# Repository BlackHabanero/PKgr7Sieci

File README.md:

# Projekt kompetencyjny grupa 7 - "Sieci przemysłowe"
Stworzyliśmy sieć przemysłową złożoną z CAN, EIA485, światłowodu oraz podsieci radiowej
w salach na trzecim piętrze budynku CTI Politechniki Łódzkiej

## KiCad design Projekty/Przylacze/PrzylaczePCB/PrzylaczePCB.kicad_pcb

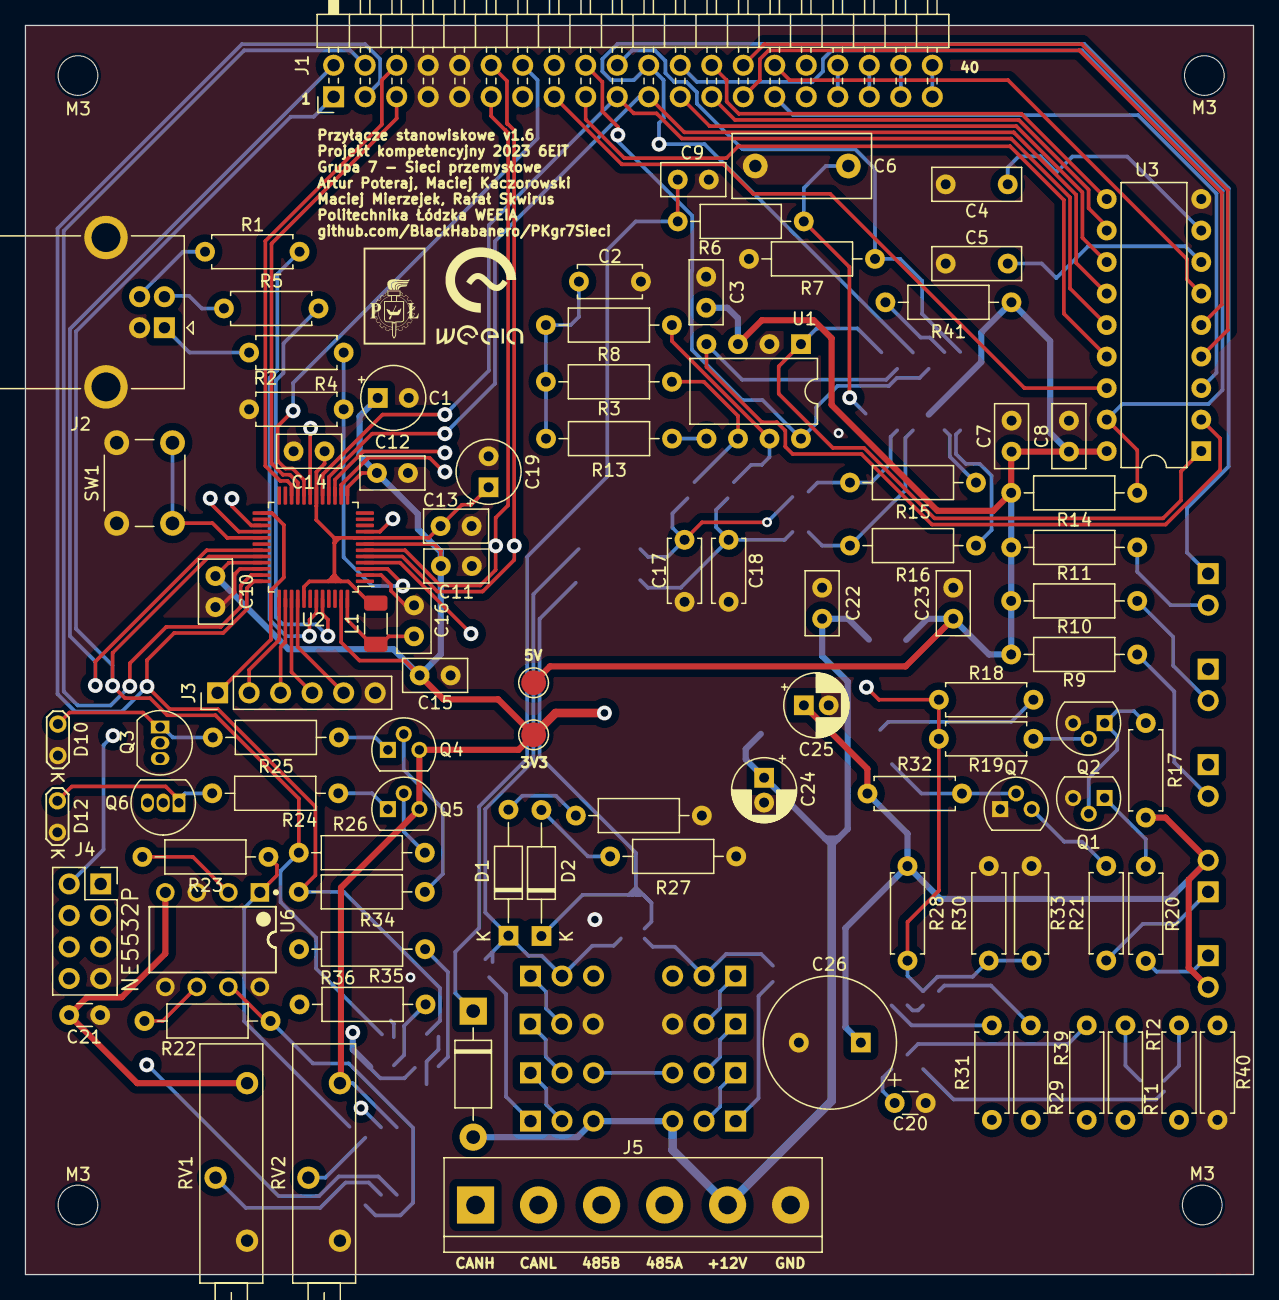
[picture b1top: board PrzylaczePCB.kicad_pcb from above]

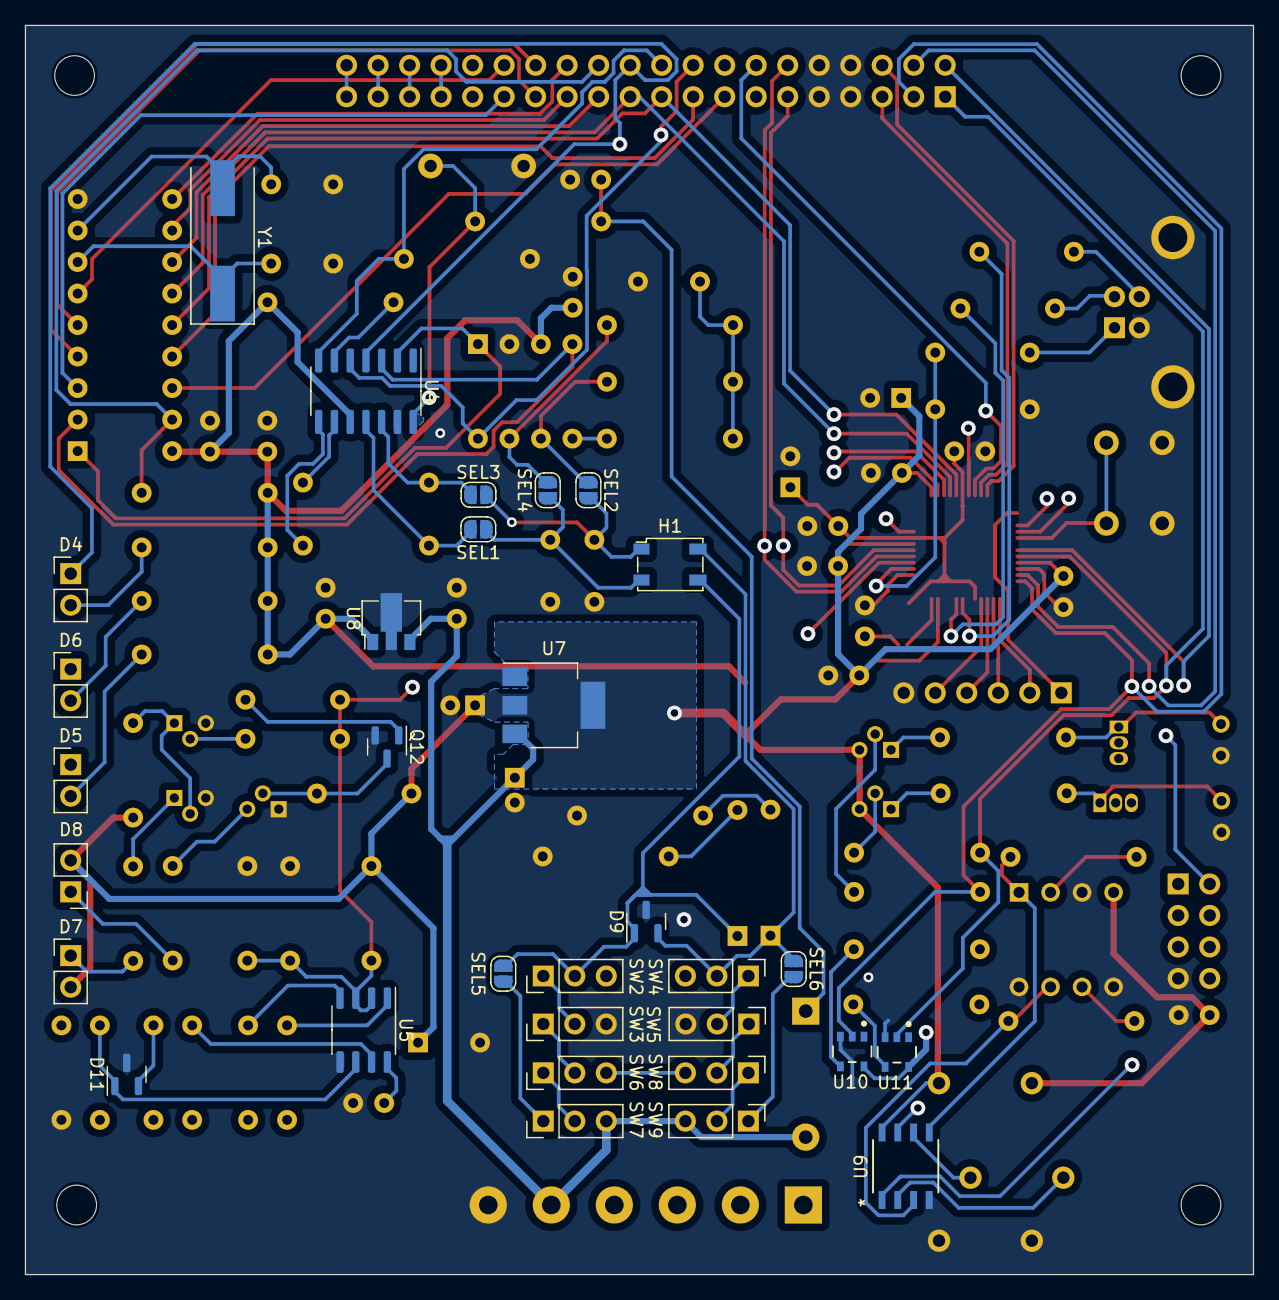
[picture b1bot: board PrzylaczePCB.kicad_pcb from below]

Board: 4 copper layers, 99.0 x 100.7 mm, 127 parts (31 on the bottom side), 104 nets.

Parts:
C1: 4.7μ; CP_Radial_Tantal_D5.0mm_P2.50mm
C2: 4n7; C_Disc_D5.0mm_W2.5mm_P5.00mm
C3, C7, C8, C9, C10, C11, C12, C13, C14, C15, C16, C23: 100n; C_Disc_D5.0mm_W2.5mm_P2.50mm
C4, C5: 15p; C_Disc_D7.0mm_W2.5mm_P5.00mm
C6: 10n; C_Disc_D11.0mm_W5.0mm_P7.50mm
C17, C18: 150p; C_Disc_D5.0mm_W2.5mm_P5.00mm
C19: 2.2μ; CP_Radial_Tantal_D5.0mm_P2.50mm
C20: 0.1 uF; C_Disc_D3.0mm_W1.6mm_P2.50mm
C21: 100n; C_Disc_D3.0mm_W1.6mm_P2.50mm
C22: 330n; C_Disc_D5.0mm_W2.5mm_P2.50mm
C24: 1u; CP_Radial_D5.0mm_P2.00mm
C25: 4.7u; CP_Radial_D5.0mm_P2.00mm
C26: 10 uF; CP_Radial_Tantal_D10.5mm_P5.00mm
D1, D2: Zener 10V; D_DO-35_SOD27_P10.16mm_Horizontal
D3: 1N4001; D_DO-41_SOD81_P10.16mm_Horizontal
D4, D5, D6: LED; PinHeader_1x02_P2.54mm_Vertical
D7: LTL-307ELC; PinHeader_1x02_P2.54mm_Vertical
D8: L-7113LYD; PinHeader_1x02_P2.54mm_Vertical
D9: PESD2IVN24-TR; SOT-23
D10, D12: LED; TestPoint_2Pads_Pitch2.54mm_Drill0.8mm
D11: SM712_SOT23; SOT-23
H1: B82787C0104H002; 4Pin_COMMON_MODE_CHOKE_B82787C0104H002
J1: Conn_02x20_Odd_Even; PinHeader_2x20_P2.54mm_Horizontal
J2: USB_B; USB_B_OST_USB-B1HSxx_Horizontal
J3: Conn_01x06; PinHeader_1x06_P2.54mm_Vertical
J4: Conn_02x04_Odd_Even; PinSocket_2x04_P2.54mm_Vertical
J5: Screw_Terminal_01x06; TerminalBlock_bornier-6_P5.08mm
L1: 10u; L_1206_3216Metric_Pad1.22x1.90mm_HandSolder
M3, M3#2, M3#3, M3#4: MountingHole_3.2mm_M3
Q1, Q2: BC547; TO-92L
Q3, Q6: BC547; TO-92_Inline
Q4, Q5: 2N3904; TO-92L
Q7: BC557; TO-92L
Q12: 2N7002; SOT-23
R1, R5: 27; R_Axial_DIN0207_L6.3mm_D2.5mm_P7.62mm_Horizontal
R2: 27k; R_Axial_DIN0207_L6.3mm_D2.5mm_P7.62mm_Horizontal
R3, R8: 62; R_Axial_DIN0207_L6.3mm_D2.5mm_P10.16mm_Horizontal
R4: 47k; R_Axial_DIN0207_L6.3mm_D2.5mm_P7.62mm_Horizontal
R6: 1-2k; R_Axial_DIN0207_L6.3mm_D2.5mm_P10.16mm_Horizontal
R7: 1k; R_Axial_DIN0207_L6.3mm_D2.5mm_P10.16mm_Horizontal
R9: R(D); R_Axial_DIN0207_L6.3mm_D2.5mm_P10.16mm_Horizontal
R10: R(D)/750; R_Axial_DIN0207_L6.3mm_D2.5mm_P10.16mm_Horizontal
R11: R(D3); R_Axial_DIN0207_L6.3mm_D2.5mm_P10.16mm_Horizontal
R12, R27: 1; R_Axial_DIN0207_L6.3mm_D2.5mm_P10.16mm_Horizontal
R13: 300; R_Axial_DIN0207_L6.3mm_D2.5mm_P10.16mm_Horizontal
R14, R26, R34, R41: 10k; R_Axial_DIN0207_L6.3mm_D2.5mm_P10.16mm_Horizontal
R15: Rrtl; R_Axial_DIN0207_L6.3mm_D2.5mm_P10.16mm_Horizontal
R16: Rrth; R_Axial_DIN0207_L6.3mm_D2.5mm_P10.16mm_Horizontal
R17, R18, R19: 1.8k; R_Axial_DIN0207_L6.3mm_D2.5mm_P7.62mm_Horizontal
R20, R21, R39, R40: 750; R_Axial_DIN0207_L6.3mm_D2.5mm_P7.62mm_Horizontal
R22, R23: 1M; R_Axial_DIN0207_L6.3mm_D2.5mm_P10.16mm_Horizontal
R24, R25: R; R_Axial_DIN0207_L6.3mm_D2.5mm_P10.16mm_Horizontal
R28: 36k; R_Axial_DIN0207_L6.3mm_D2.5mm_P7.62mm_Horizontal
R29, R30, R31, R33: 10k; R_Axial_DIN0207_L6.3mm_D2.5mm_P7.62mm_Horizontal
R32: 18k; R_Axial_DIN0207_L6.3mm_D2.5mm_P7.62mm_Horizontal
R35, R36: 600; R_Axial_DIN0207_L6.3mm_D2.5mm_P10.16mm_Horizontal
RT1, RT2: 62; R_Axial_DIN0207_L6.3mm_D2.5mm_P7.62mm_Horizontal
RV1, RV2: 20k; Potentiometer_Bourns_3006P_Horizontal
SEL1, SEL2, SEL3, SEL4, SEL5, SEL6: SolderJumper-2_P1.3mm_Open_RoundedPad1.0x1.5mm
SW1: SW_Push; SW_PUSH_6mm
SW2, SW3, SW4, SW5, SW6, SW7, SW8, SW9: SW_SPDT; PinHeader_1x03_P2.54mm_Vertical
U1: MCP2561-E-P; DIP-8_W7.62mm
U2: ATSAM4S2AA-AU; LQFP-48_7x7mm_P0.5mm
U3: MCP2515-xSO; DIP-18_W7.62mm
U4: TJA1055T_3_C,518; SO-14_3.9x8.65mm_P1.27mm
U5: MAX3485; SO-8_3.9x4.9mm_P1.27mm
U6: NE5532P; Texas_Instruments-NE5532P
U7: LDL1117S33R; SOT-223-3_TabPin2
U8: DI78M05UAB; SOT-89-3
U9: TLV3202AID
U10, U11: 74AHC1G04; Nexperia-SOT753-10_2018-0-0
Y1: 20MHz; Crystal_SMD_HC49-SD

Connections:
+3.3V: C1.1, C10.1, C11.1, C12.1, C15.1, C20.1, C21.2, C25.1, C26.1, D7.2 (A), D8.2 (A), J4.6, J4.8, Q4.3 (C), Q5.3 (C), R17.2, R28.1, R29.1, R31.1, R32.1, R39.1, RV1.1, RV2.1, U2.7 (VDDIN), U2.13 (VDDIO), U2.33 (VDDIO), U2.47 (VDDIO), U5.8 (VCC), U6.4 (VCC-), U7.2 (Vout), U9.8 (VCC), U10.5 (VCC), U11.5 (VCC)
+5V: C3.2, C7.2, C8.2, C23.1, R9.2, R10.2, R11.2, R14.2, R41.1, U1.3 (VDD), U3.18 (VDD), U4.10 (VCC), U8.1 (Vout)
+12V: C22.2, C24.1, D3.2 (A), J5.5, SW7.3 (C), SW9.3 (C), U7.3 (Vin), U8.3 (Vin)
A: D11.1 (A1), J1.35, J1.36, J5.4, R40.1, RT2.2, U5.6 (A)
B: D11.2 (A2), J1.33, J1.34, J5.3, R39.2, RT1.1, U5.7 (B)
CANH: J1.37, J1.38, J5.1, SEL6.2, SW9.1 (A)
CANH_FT: R16.2, SEL1.1, U4.11 (CANH)
CANH_HS: R8.1, SEL4.1, U1.7 (CANH)
CANL: J1.39, J1.40, J5.2, SEL5.2, SW7.1 (A)
CANL_FT: R15.2, SEL3.1, U4.12 (CANL)
CANL_HS: R3.2, SEL2.1, U1.6 (CANL)
CS0: J1.14, J4.5, U2.20 (PA11/PGMM3)
CS3: J1.15, U2.27 (PA5/PGMRDY), U3.16 (~CS)
EN: J1.16, R41.2, U2.15 (PA15/PGMD3), U4.6 (EN)
ERR: D4.1 (K), J1.22, U2.9 (PA17/PGMD5/AD0), U4.4 (~ERR)
GND: C1.2, C2.2, C3.1, C4.1, C5.1, C6.1, C7.1, C8.1, C9.1, C10.2, C11.2, C12.2, C13.2, C14.2, C15.2, C16.2, C17.2, C18.2, C19.2, C20.2, C21.1, C22.1, C23.2, C24.2, C25.2, C26.2, D9.3 (A), D10.1 (K), D11.3 (common), D12.1 (K), J1.7, J1.8, J1.9, J1.10, J2.4 (GND), J2.5 (Shield), J3.6, J4.7, J5.6, Q1.3 (E), Q2.3 (E), Q7.1 (C), Q12.2 (S), R4.2, R7.2, R12.1, R27.1, R30.2, R33.2, R40.2, RV1.3, RV2.3, SW1.1, SW3.3 (C), SW5.3 (C), U1.2 (VSS), U2.2 (GND), U2.34 (GND), U3.9 (VSS), U4.13 (GND), U5.5 (GND), U6.3 (IN1+), U6.5 (IN2+), U6.8 (VCC+), U7.1 (GND), U8.2 (GND), U9.4 (GND), U10.3 (GND), U11.3 (GND)
INT: J1.23, U3.12 (~INT)
MISO: J1.17, J4.1, U2.19 (PA12/PGMD0), U3.15 (SO)
MOSI: J1.19, J4.4, U2.17 (PA13/PGMD1), U3.14 (SI)
unnamed: C2.1, R3.1, R8.2, R13.2
unnamed: C17.1, H1.1, SEL2.2, SEL3.2
unnamed: C18.1, H1.2, SEL1.2, SEL4.2
unnamed: D1.2 (A), R12.2
unnamed: D1.1 (K), D9.2 (K), H1.4, SEL6.1, SW4.2 (B)
unnamed: D2.2 (A), R27.2
unnamed: D2.1 (K), D9.1 (K), H1.3, SEL5.1, SW2.2 (B)
unnamed: C9.2, D3.1 (K), R6.2
unnamed: D4.2 (A), R11.1
unnamed: D5.2 (A), R9.1
unnamed: D6.2 (A), R10.1
unnamed: D7.1 (K), R20.1
unnamed: D8.1 (K), R21.1
unnamed: D10.2 (A), Q3.1 (C), R25.1
unnamed: D12.2 (A), Q6.1 (C), R24.2
unnamed: J2.3 (D+), R1.2
unnamed: J2.2 (D-), R5.2
unnamed: J2.1 (VBUS), R2.2
unnamed: J3.1, U2.25 (TDI/PB4)
unnamed: J3.2, U2.37 (TDO/TRACESWO/PB5)
unnamed: J3.3, U2.38 (JTAGSEL)
unnamed: J3.4, U2.39 (TMS/SWDIO/PB6)
unnamed: J3.5, U2.40 (TCK/SWCLK/PB7)
unnamed: Q1.2 (B), Q2.1 (C), R17.1
unnamed: Q1.1 (C), R20.2
unnamed: Q2.2 (B), R19.1
unnamed: Q3.2 (B), R35.1
unnamed: Q3.3 (E), R22.2, U6.6 (IN2-)
unnamed: Q4.2 (B), R34.2
unnamed: Q4.1 (E), R25.2
unnamed: Q5.2 (B), R26.2
unnamed: Q5.1 (E), R24.1
unnamed: Q6.2 (B), R36.1
unnamed: Q6.3 (E), R23.1, U6.2 (IN1-)
unnamed: Q7.3 (E), R21.2
unnamed: Q7.2 (B), Q12.3 (D), R32.2
unnamed: Q12.1 (G), R18.2
unnamed: RT1.2, RT2.1
unnamed: SW2.1 (A), SW3.2 (B)
unnamed: SW3.1 (A), SW6.2 (B)
unnamed: SW4.1 (A), SW5.2 (B)
unnamed: SW5.1 (A), SW8.2 (B)
unnamed: SW6.1 (A), SW7.2 (B)
unnamed: SW6.3 (C), SW8.3 (C)
unnamed: SW8.1 (A), SW9.2 (B)
unnamed: R13.1, U1.5 (SPLIT)
unnamed: R1.1, U2.43 (DDM/PB10)
unnamed: R5.1, U2.44 (DDP/PB11)
unnamed: C13.1, C14.1, C19.1, L1.1, U2.8 (VDDOUT), U2.18 (VDDCORE), U2.41 (VDDCORE)
unnamed: C16.1, L1.2, U2.48 (VDDPLL)
unnamed: SW1.2, U2.29 (~RST)
unnamed: C4.2, U3.8 (OSC1), Y1.2
unnamed: C5.2, U3.7 (OSC2), Y1.1
unnamed: C6.2, R6.1, U4.14 (BAT)
unnamed: R16.1, U4.8 (RTH)
unnamed: R15.1, U4.9 (RTL)
OPTO1_NOT_TX: R35.2, U10.4
OPTO1_OPAMP: R22.1, U6.7 (OUT2), U9.3 (1IN+)
OPTO1_POT: RV1.2, U9.2 (1IN-)
OPTO1_RX: J1.4, U2.35 (PA1/PGMEN1), U9.1 (1OUT)
OPTO1_TX: J1.3, R34.1, U2.36 (PA0/PGMEN0), U10.2
OPTO2_NOT_TX: R36.2, U11.4
OPTO2_OPAMP: R23.2, U6.1 (OUT1), U9.5 (2IN+)
OPTO2_POT: RV2.2, U9.6 (2IN-)
OPTO2_RX: J1.2, U2.31 (PA3), U9.7 (2OUT)
OPTO2_TX: J1.1, R26.1, U2.32 (PA2/PGMEN2), U11.2
RADIO_IRQ: J4.2, U2.4 (PB1/AD5)
RESET: J1.24, R14.1, U3.17 (~RESET)
RX0BF: J1.25, U3.11 (~RX0BF)
RX1BF: J1.26, U3.10 (~RX1BF)
RXD: D6.1 (K), J1.31, U1.4 (RXD), U3.2 (RXCAN), U4.3 (RXD)
RX_MCU: J1.12, R31.2, U2.5 (PB2/AD6), U5.1 (RO)
RX/TX ENABLE: J1.13, R18.1, R19.2, R28.2, R30.1, R33.1, U2.28 (PA4/PGMNCMD), U5.2 (~RE), U5.3 (DE)
SOF: J1.29, U3.3 (CLKOUT/SOF)
SPCK: J1.21, J4.3, U2.16 (PA14/PGMD2), U3.13 (SCK)
STBY: J1.18, U1.8 (STBY), U2.14 (PA16/PGMD4), U4.5 (~STB)
TX0RTS: J1.28, U3.4 (~TX0RTS)
TX1RTS: J1.27, U3.5 (~TX1RTS)
TX2RTS: J1.30, U3.6 (~TX2RTS)
TXD: D5.1 (K), J1.32, U1.1 (TXD), U3.1 (TXCAN), U4.2 (TXD)
TX_MCU: J1.11, R29.2, U2.6 (PB3/AD7), U5.4 (DI)
UART0_RX: J1.6, U2.22 (PA9/PGMM1)
UART0_TX: J1.5, U2.21 (PA10/PGMM2)
USBMON: R2.1, R4.1, U2.3 (PB0/AD4)
WAKE: J1.20, R7.1, U4.7 (~WAKE)

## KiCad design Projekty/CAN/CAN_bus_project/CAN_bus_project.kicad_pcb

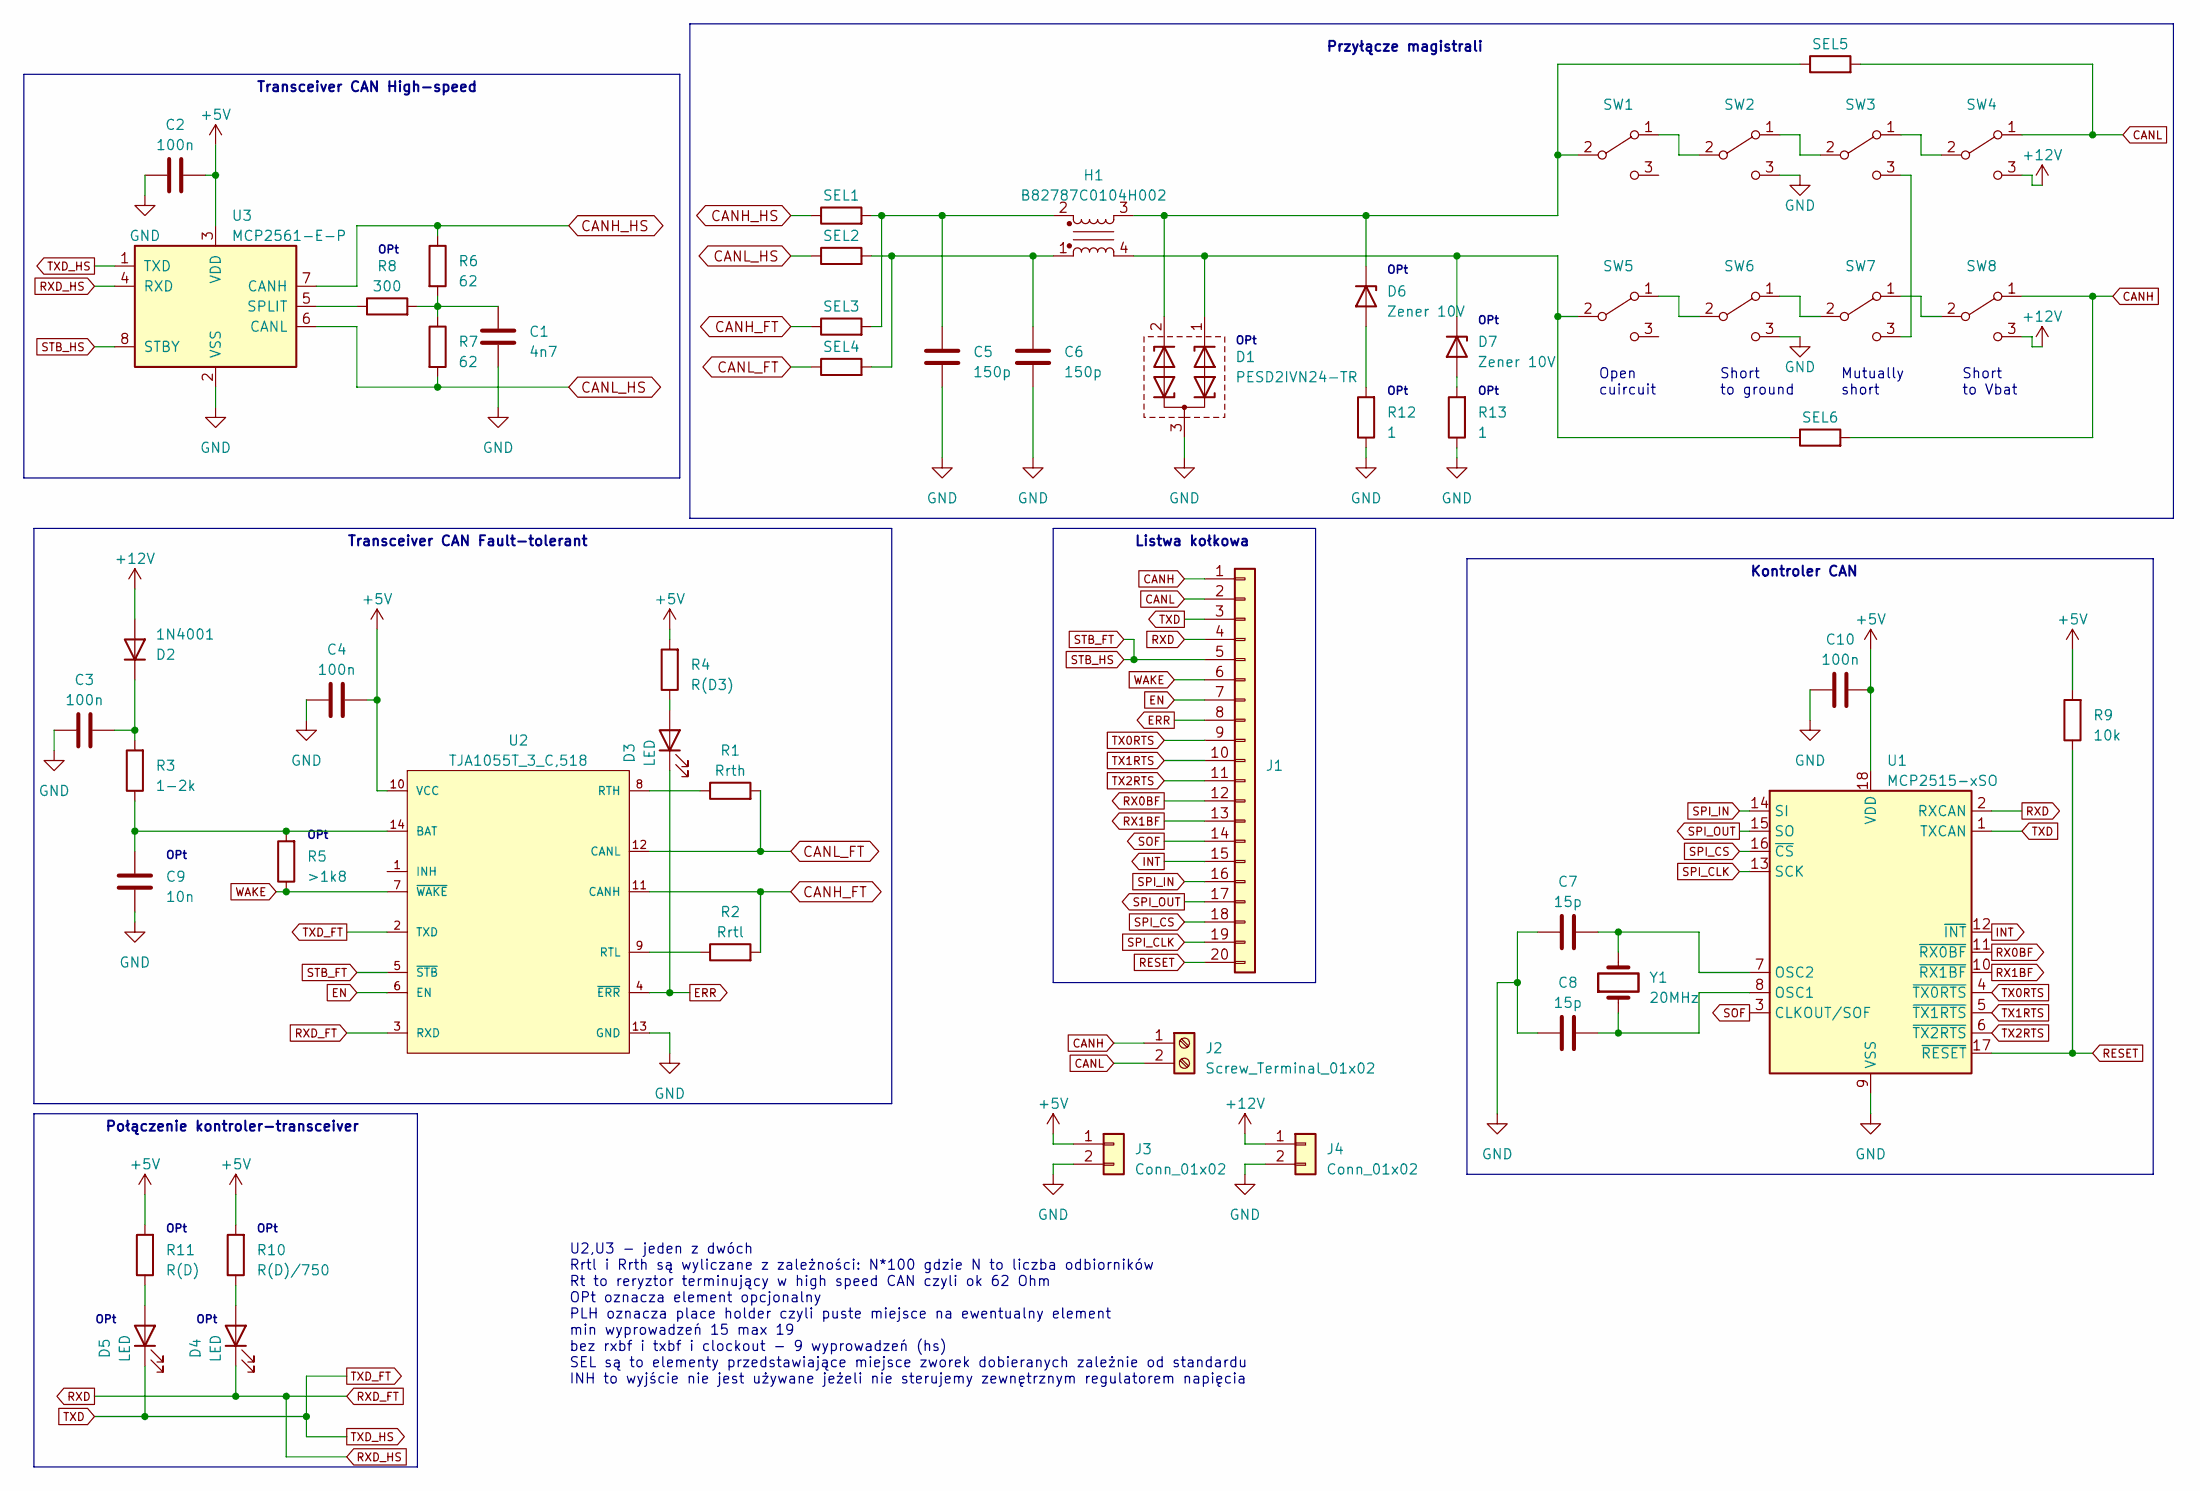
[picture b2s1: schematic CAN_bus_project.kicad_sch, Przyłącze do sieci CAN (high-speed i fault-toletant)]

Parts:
C1: 4n7; C_Disc_D5.0mm_W2.5mm_P5.00mm
C2, C3, C4, C10: 100n; C_Disc_D5.0mm_W2.5mm_P2.50mm
C5, C6: 150p; C_Disc_D5.0mm_W2.5mm_P5.00mm
C7, C8: 15p; C_Disc_D7.0mm_W2.5mm_P5.00mm
C9: 10n; C_Disc_D11.0mm_W5.0mm_P7.50mm
D1: PESD2IVN24-TR; SOT-23
D2: 1N4001; D_DO-41_SOD81_P10.16mm_Horizontal
D3, D4, D5: LED; 2PAD_WIRE
D6, D7: Zener 10V; D_DO-35_SOD27_P10.16mm_Horizontal
H1: B82787C0104H002; 4Pin_COMMON_MODE_CHOKE_B82787C0104H002
J1: Conn_01x20; PinSocket_2x20_P2.54mm_Vertical
J2: Screw_Terminal_01x02; Samtec_HPM-02-05-x-S_Straight_1x02_Pitch5.08mm
J3, J4: Conn_01x02
R1: Rrth; R_Axial_DIN0207_L6.3mm_D2.5mm_P10.16mm_Horizontal
R2: Rrtl; R_Axial_DIN0207_L6.3mm_D2.5mm_P10.16mm_Horizontal
R3: 1-2k; R_Axial_DIN0207_L6.3mm_D2.5mm_P10.16mm_Horizontal
R4: R(D3); R_Axial_DIN0207_L6.3mm_D2.5mm_P10.16mm_Horizontal
R5: >1k8; R_Axial_DIN0207_L6.3mm_D2.5mm_P10.16mm_Horizontal
R6, R7: 62; R_Axial_DIN0207_L6.3mm_D2.5mm_P10.16mm_Horizontal
R8: 300; R_Axial_DIN0207_L6.3mm_D2.5mm_P10.16mm_Horizontal
R9: 10k; R_Axial_DIN0207_L6.3mm_D2.5mm_P10.16mm_Horizontal
R10: R(D)/750; R_Axial_DIN0207_L6.3mm_D2.5mm_P10.16mm_Horizontal
R11: R(D); R_Axial_DIN0207_L6.3mm_D2.5mm_P10.16mm_Horizontal
R12, R13: 1; R_Axial_DIN0207_L6.3mm_D2.5mm_P10.16mm_Horizontal
SEL1, SEL2, SEL3, SEL4, SEL5, SEL6: R_0805_2012Metric
SW1, SW2, SW3, SW4, SW5, SW6, SW7, SW8: SW_SPDT; 3PAD_WIRE_SWITCH
U1: MCP2515-xSO; DIP-18_W7.62mm
U2: TJA1055T_3_C,518; SO-14_3.9x8.65mm_P1.27mm; mouser part number 771-TJA1055T3C518; digikey description IC TRANSCEIVER HALF 1/1 14SO
U3: MCP2561-E-P; DIP-8_W7.62mm
Y1: 20MHz; Crystal_SMD_HC49-SD_HandSoldering

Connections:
+5V: C2.2, C4.2, C10.2, J3.1, R4.2, R9.2, R10.2, R11.2, U1.18 (VDD), U2.10 (VCC), U3.3 (VDD)
+12V: D2.2 (A), J4.1, SW4.3 (C), SW8.3 (C)
CANH: J1.1, J2.1, SEL6.2, SW8.1 (A)
CANH_FT: R2.2, SEL3.1, U2.11 (CANH)
CANH_HS: R6.1, SEL1.1, U3.7 (CANH)
CANL: J1.2, J2.2, SEL5.2, SW4.1 (A)
CANL_FT: R1.2, SEL4.1, U2.12 (CANL)
CANL_HS: R7.2, SEL2.1, U3.6 (CANL)
EN: J1.7, U2.6 (EN)
ERR: D3.1 (K), J1.8, U2.4 (~ERR)
GND: C1.2, C2.1, C3.1, C4.1, C5.2, C6.2, C7.1, C8.1, C9.1, C10.1, D1.3 (A), J3.2, J4.2, R12.1, R13.1, SW2.3 (C), SW6.3 (C), U1.9 (VSS), U2.13 (GND), U3.2 (VSS)
INT: J1.15, U1.12 (~INT)
unnamed: C1.1, R6.2, R7.1, R8.2
unnamed: C5.1, H1.2, SEL1.2, SEL3.2
unnamed: C6.1, H1.1, SEL2.2, SEL4.2
unnamed: C3.2, D2.1 (K), R3.2
unnamed: D3.2 (A), R4.1
unnamed: D4.2 (A), R10.1
unnamed: D5.2 (A), R11.1
unnamed: D6.2 (A), R12.2
unnamed: D1.2 (K), D6.1 (K), H1.3, SEL5.1, SW1.2 (B)
unnamed: D7.2 (A), R13.2
unnamed: D1.1 (K), D7.1 (K), H1.4, SEL6.1, SW5.2 (B)
unnamed: SW1.1 (A), SW2.2 (B)
unnamed: SW2.1 (A), SW3.2 (B)
unnamed: SW3.1 (A), SW4.2 (B)
unnamed: SW3.3 (C), SW7.3 (C)
unnamed: SW5.1 (A), SW6.2 (B)
unnamed: SW6.1 (A), SW7.2 (B)
unnamed: SW7.1 (A), SW8.2 (B)
unnamed: C8.2, U1.8 (OSC1), Y1.1
unnamed: C7.2, U1.7 (OSC2), Y1.2
unnamed: C9.2, R3.1, R5.2, U2.14 (BAT)
unnamed: R1.1, U2.8 (RTH)
unnamed: R2.1, U2.9 (RTL)
unnamed: R8.1, U3.5 (SPLIT)
RESET: J1.20, R9.1, U1.17 (~RESET)
RX0BF: J1.12, U1.11 (~RX0BF)
RX1BF: J1.13, U1.10 (~RX1BF)
RXD: D4.1 (K), J1.4, U1.2 (RXCAN), U2.3 (RXD), U3.4 (RXD)
SOF: J1.14, U1.3 (CLKOUT/SOF)
SPI_CLK: J1.19, U1.13 (SCK)
SPI_CS: J1.18, U1.16 (~CS)
SPI_IN: J1.16, U1.14 (SI)
SPI_OUT: J1.17, U1.15 (SO)
STB_FT: J1.5, U2.5 (~STB), U3.8 (STBY)
TX0RTS: J1.9, U1.4 (~TX0RTS)
TX1RTS: J1.10, U1.5 (~TX1RTS)
TX2RTS: J1.11, U1.6 (~TX2RTS)
TXD: D5.1 (K), J1.3, U1.1 (TXCAN), U2.2 (TXD), U3.1 (TXD)
WAKE: J1.6, R5.1, U2.7 (~WAKE)

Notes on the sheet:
Listwa kołkowa
OPt
Transceiver CAN Fault-tolerant
Kontroler CAN
Transceiver CAN High-speed
Połączenie kontroler-transceiver
Short to Vbat
Przyłącze magistrali
U2,U3 - jeden z dwóch Rrtl i Rrth są wyliczane z zależności: N*100 gdzie N to liczba odbiorników Rt to reryztor terminujący w high speed CAN czyli ok 62 Ohm OPt oznacza element opcjonalny PLH oznacza place holder czyli puste miejsce na ewentualny element min wyprowadzeń 15 max 19 bez rxbf i txbf i 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
Short to ground
Open cuircuit
Mutually short

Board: 2 copper layers, 51 parts (0 on the bottom side), 51 nets, no tracks yet.

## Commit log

2023-03-04 Tworzy bazową przestrzeń projektu
2023-03-04 Uzupełnia notatki ze spotkania 3. marca
2023-03-08 Uzupełnia notatki ze spotkania 8. marca
2023-03-09 Uzupełnia notatki ze spotkania 9. marca
    zmienia format poprzednich notatek (Plain text -> Markdown)
2023-03-10 Uzupełnia notatki ze spotkania 10. marca
2023-03-10 Rozpoczyna pracę nad przełącznikiem ethernet do POF
2023-03-17 Uzupełnia notatki ze spotkania 17. marca
2023-03-22 Uzupełnia notatki ze spotkania 22. marca
2023-05-09 Schemat elektryczny EIA485 v0.1
2023-05-09 OPTO: Dodaje wyniki analizy LED w roli fotodiody
2023-05-09 Uzupełnia notatki ze spotkania 24. marca
2023-05-09 Przyłącze - schemat elektryczny v0.1
2023-05-09 Schemat elektryczny CAN v0.1
2023-05-09 Schemat elektryczny EIA485 v0.2
2023-05-09 Kosztorys sieci CAN
2023-05-09 Aktualizacja kosztorysu sieci CAN
2023-05-09 Update kosztorysu CAN
2023-05-09 Schemat elektryczny EIA485 v0.3
2023-05-09 Schemat elektryczny CAN v0.2
2023-05-09 Całkowity kosztorys dla EIA485 i CAN HS
2023-05-09 Schemat elektryczny CAN v0.3
2023-05-09 Schemat elektryczny EIA485 v0.4
2023-05-09 Uzupełnia notatki ze spotkania 31. marca
2023-05-09 Dodanie wstępnego projektu sieci
2023-05-09 Aktualizuje README.md
2023-05-09 Połączenie w jeden schemat przyłącza sieci EIA485
2023-05-09 Porządki w repozytorium
2023-05-09 Przyłącze - schemat elektryczny v1.0
2023-05-09 Przyłącze - schemat elektryczny v1.1
2023-05-09 Dodanie planu rozprowadzenia sieci dla sali 305
2023-05-09 Plan sieci - całe piętro
2023-05-09 Przyłącze - schemat elektryczny v1.2
2023-05-09 Przyłącze - projekt PCB v0.1
2023-05-09 Aktualizacja planu sieci
2023-05-09 Przyłącze - projekt PCB v0.4
2023-05-09 Przyłącze - projekt PCB v0.2
2023-05-09 Przyłącze - projekt PCB v0.3
2023-05-09 Przyłącze - projekt PCB v0.5
2023-05-09 Przyłącze - projekt PCB v1.1
2023-05-09 Przyłącze - projekt PCB v1.0
2023-05-09 Przyłącze - projekt PCB v1.2
2023-05-09 Przyłącze - projekt PCB v1.3
2023-05-16 Aktualizacja kosztorysów
2023-05-16 Dodatkowy kosztorys CAN fault-tolerant
2023-05-16 Usunięto nagranie z inspekcji podsufitki sali 305 z 24. marca
2023-05-16 Plan sieci v1.0
2023-05-16 Przyłącze - projekt PCB v1.4
2023-05-16 Plan sieci v1.2
2023-05-16 Plan sieci v1.1
2023-05-16 Przyłącze - schemat elektryczny v1.3
2023-05-16 Przyłącze - projekt PCB v1.3.1
2023-05-21 Oprogramowanie do obsługi CAN pod STM32L476RG v0.1
2023-05-22 Oprogramowanie do obsługi CAN pod STM32L476RG v0.2
2023-05-23 Oprogramowanie do obsługi CAN pod STM32L476RG v0.3
2023-05-23 Oprogramowanie do obsługi CAN pod STM32L476RG v0.4
2023-05-30 Przyłącze - projekt PCB v1.4.1
2023-05-30 Plan sieci v2.0 i aktualizacja kosztorysów
2023-06-05 Projekt obudowy v0.1
2023-06-26 Oprogramowanie do obsługi CAN pod STM32L476RG v0.5
2023-06-26 Przyłącze - projekt PCB v1.5
2023-06-29 Przyłącze - projekt PCB v1.5.1
2023-06-29 Przyłącze - projekt PCB v1.5.2
2023-07-15 Przyłącze - schemat elektryczny v1.4
2023-07-16 Przyłącze - schemat elektryczny v1.4.1
2023-07-30 Przyłącze - projekt PCB v1.6
2023-08-01 Obudowa - projekt, pliki wykonawcze, pdf v0.7 i v0.8
2023-08-15 PeCeBe wersja Final Omega Prime Ultimate Fatality
2023-08-22 Kosztorys zamówienia uzupełniające
2023-08-30 Zestawienie kosztów
2023-09-09 Prezentacja końcowa
2023-09-09 Środowiskowa ocena cyklu życia
2023-09-09 Aktualizacja dokumentacji przyłączy
2023-09-11 Rozmieszczenie i wykaz elementów na płytce interfejsu sieci w wersji 1.6
2023-09-11 dodano BoM
